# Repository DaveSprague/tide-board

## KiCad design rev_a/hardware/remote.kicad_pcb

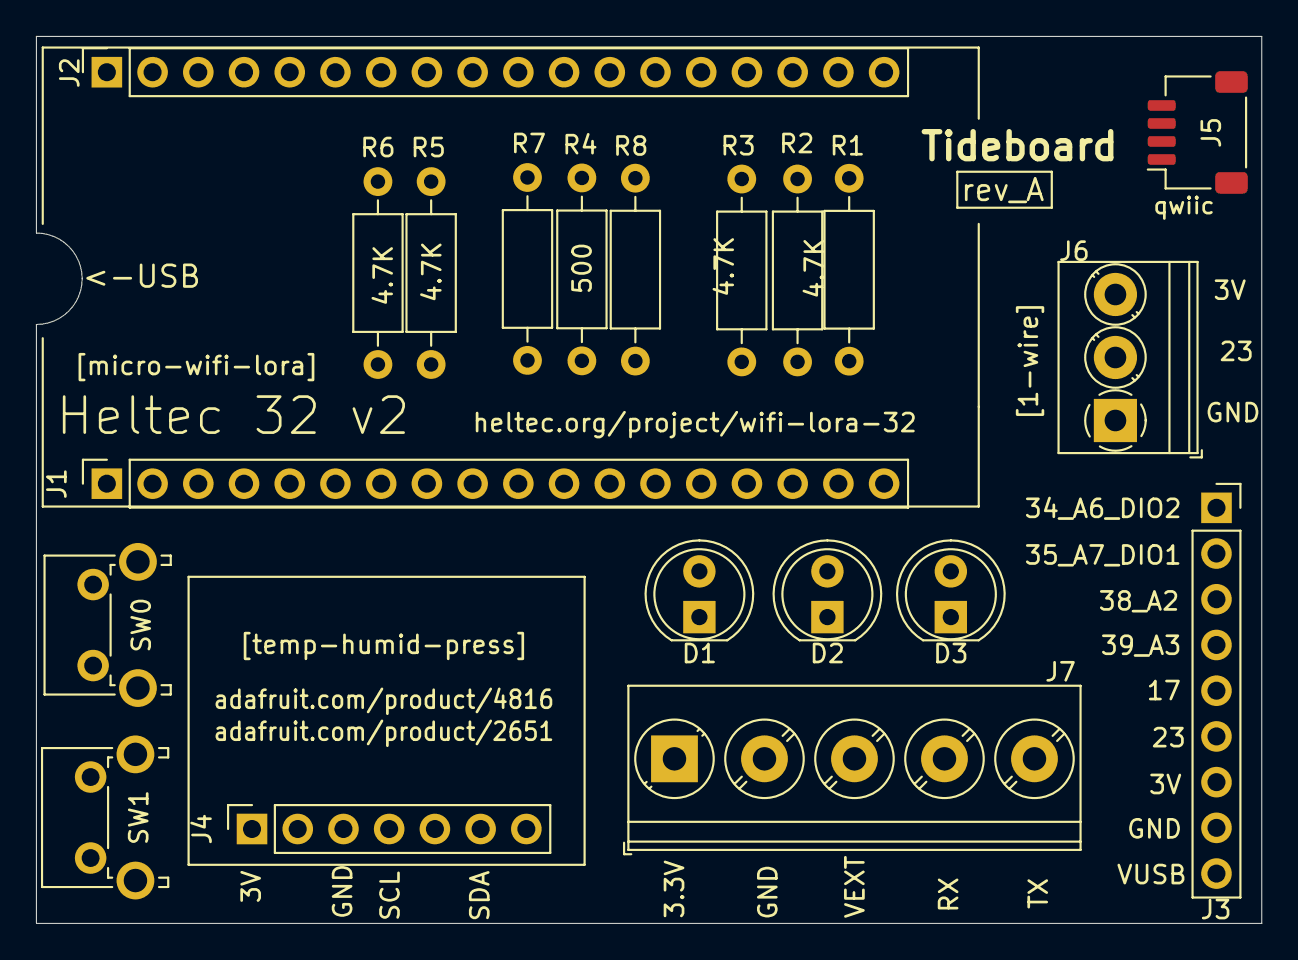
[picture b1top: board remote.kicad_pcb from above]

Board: 2 copper layers, 68.1 x 49.3 mm, 20 parts (0 on the bottom side), 16 nets, no tracks yet.

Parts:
D1, D2, D3: LED; LED_D5.0mm
J1, J2: Conn_01x18_Female; PinSocket_1x18_P2.54mm_Vertical
J3: Conn_01x09_Female; PinSocket_1x09_P2.54mm_Vertical
J4: Conn_01x07_Female; PinSocket_1x07_P2.54mm_Vertical
J5: Conn_01x04_Female; JST_SH_SM04B-SRSS-TB_1x04-1MP_P1.00mm_Horizontal
J6: Screw_Terminal_01x03; TerminalBlock_Phoenix_PT-1,5-3-3.5-H_1x03_P3.50mm_Horizontal
J7: Screw_Terminal_01x05; TerminalBlock_Phoenix_PT-1,5-5-5.0-H_1x05_P5.00mm_Horizontal
R1, R2, R3: R; R_Axial_DIN0207_L6.3mm_D2.5mm_P10.16mm_Horizontal
R4, R7, R8: 500R; R_Axial_DIN0207_L6.3mm_D2.5mm_P10.16mm_Horizontal
R5, R6: 4.7K; R_Axial_DIN0207_L6.3mm_D2.5mm_P10.16mm_Horizontal
SW0, SW1: SW_Push; SW_Tactile_SPST_Angled_PTS645Vx58-2LFS

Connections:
5V: J1.2, J3.9
17: D1.2, D2.2, D3.2, J1.17, J3.5
23: J1.11, J3.6, J6.2, R1.2
34_ADC6_DIO2: J2.8, J3.1
35_ADC7_DIO1: J2.9, J3.2
36_A0: J2.4, R6.2, SW0.1
37_A1: J2.5, R5.2, SW1.1
38_A2: J2.6, J3.3
39_A3: J2.7, J3.4
+3V3: J2.2, J3.7, J4.1, J5.2, J6.3, R1.1, R2.1, R3.1, R5.1, R6.1
GND: J1.1, J2.1, J3.8, J4.3, J5.1, J6.1, R4.2, R7.2, R8.2, SW0.2, SW1.2
unnamed: D1.1, R4.1
unnamed: D2.1, R7.1
unnamed: D3.1, R8.1
SCL: J1.9, J4.4, J5.4, R2.2
SDA: J2.18, J4.6, J5.3, R3.2
